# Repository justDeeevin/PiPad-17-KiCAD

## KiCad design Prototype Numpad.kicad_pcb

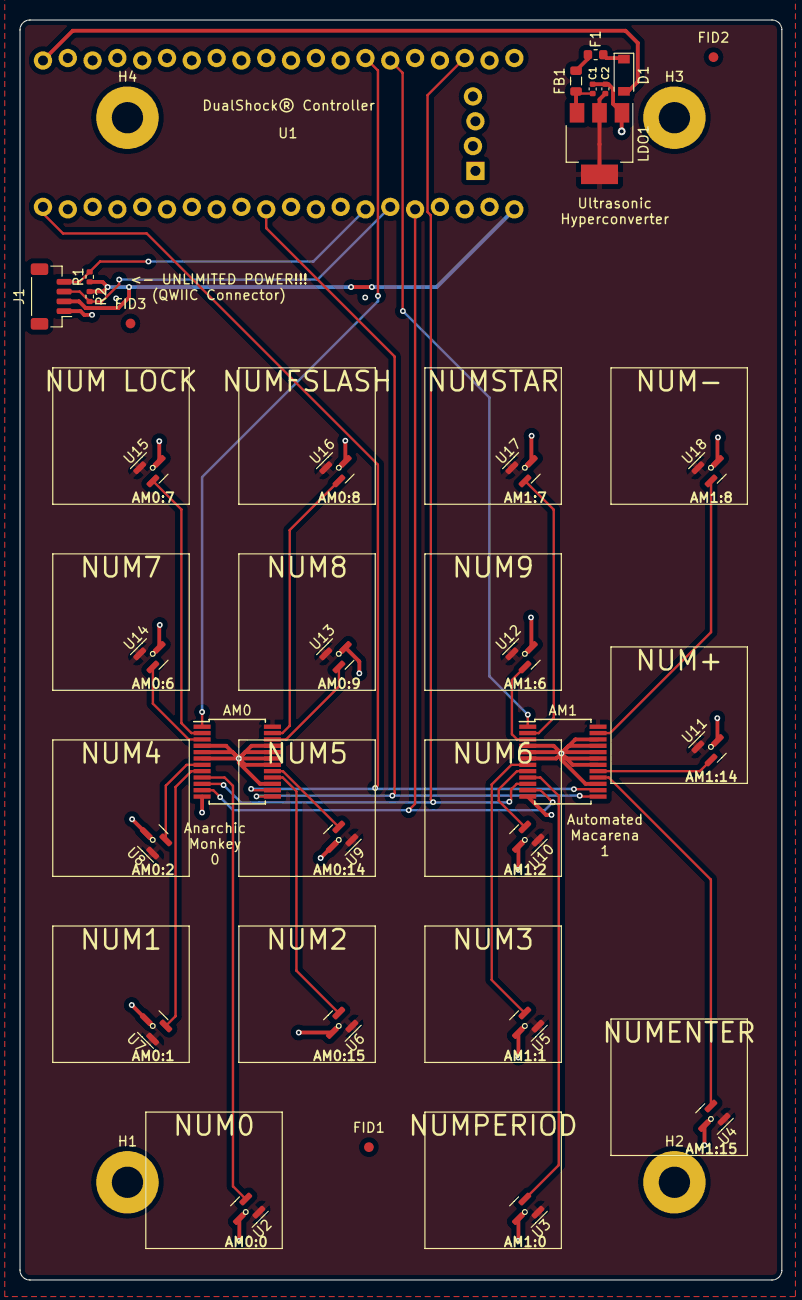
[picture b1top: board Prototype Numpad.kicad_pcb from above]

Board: 2 copper layers, 78.0 x 129.0 mm, 54 parts (1 on the bottom side), 32 nets.

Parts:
AM0, AM1: CD74HC4067SM; SSOP-24_5.3x8.2mm_P0.65mm
AM0:0: NUM0; VoidSwitch_2u_SMD
AM0:1: NUM1; VoidSwitch_1u_SMD
AM0:2: NUM4; VoidSwitch_1u_SMD
AM0:6: NUM7; VoidSwitch_1u_SMD
AM0:7: NUM LOCK; VoidSwitch_1u_SMD
AM0:8: NUMFSLASH; VoidSwitch_1u_SMD
AM0:9: NUM8; VoidSwitch_1u_SMD
AM0:14: NUM5; VoidSwitch_1u_SMD
AM0:15: NUM2; VoidSwitch_1u_SMD
AM1:0: NUMPERIOD; VoidSwitch_1u_SMD
AM1:1: NUM3; VoidSwitch_1u_SMD
AM1:2: NUM6; VoidSwitch_1u_SMD
AM1:6: NUM9; VoidSwitch_1u_SMD
AM1:7: NUMSTAR; VoidSwitch_1u_SMD
AM1:8: NUM-; VoidSwitch_1u_SMD
AM1:14: NUM+; VoidSwitch_2uv_SMD
AM1:15: NUMENTER; VoidSwitch_2uv_SMD
C1, C2: 10u; C_0402_1005Metric
D1: B5819W; D_SOD-123
F1: 500mA; Fuse_0603_1608Metric
FB1: 100 @ 100 MHz; L_0805_2012Metric
FID1, FID2, FID3: Fiducial; Fiducial_1mm_Mask2mm
H1, H2, H3, H4: MountingHole; MountingHole_3.2mm_M3_Pad
J1: QWIIC; JST_SH_BM04B-SRSS-TB_1x04-1MP_P1.00mm_Vertical
LDO1: AMS1117-3.3; SOT-223-3_TabPin2
QR*****: https://github.com/riskable/void_switch; VoidSwitch_Repo_QR_0.5mm
R1, R2: 2k2; R_0402_1005Metric
U1: BlackPill_STLINK
U2, U3, U4, U5, U6, U7, U8, U9, U10, U11, U12, U13, U14, U15, U16, U17, U18: GH39FKSW; SOT-23

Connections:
+3.3V_QWIIC: J1.2, R1.1, R2.1, U1.20 (3V3)
+3V3: AM0.24 (VCC), AM1.24 (VCC), C2.1, LDO1.2 (VO), U2.1 (VDD), U3.1 (VDD), U4.1 (VDD), U5.1 (VDD), U6.1 (VDD), U7.1 (VDD), U8.1 (VDD), U9.1 (VDD), U10.1 (VDD), U11.1 (VDD), U12.1 (VDD), U13.1 (VDD), U14.1 (VDD), U15.1 (VDD), U16.1 (VDD), U17.1 (VDD), U18.1 (VDD)
+5V: D1.2 (A), U1.40 (5V)
AM0: AM1.1 (COM), U1.26 (PA0)
AM0:0: AM0.9 (I0), U2.2 (OUT)
AM0:1: AM0.8 (I1), U7.2 (OUT)
AM0:2: AM0.7 (I2), U8.2 (OUT)
AM0:6: AM0.3 (I6), U14.2 (OUT)
AM0:7: AM0.2 (I7), U15.2 (OUT)
AM0:8: AM0.23 (I8), U16.2 (OUT)
AM0:9: AM0.22 (I9), U13.2 (OUT)
AM0:14: AM0.17 (I14), U9.2 (OUT)
AM0:15: AM0.16 (I15), U6.2 (OUT)
AM1: AM0.1 (COM), U1.27 (PA1)
AM1:0: AM1.9 (I0), U3.2 (OUT)
AM1:1: AM1.8 (I1), U10.2 (OUT)
AM1:2: AM1.7 (I2), U5.2 (OUT)
AM1:6: AM1.3 (I6), U12.2 (OUT)
AM1:7: AM1.2 (I7), U17.2 (OUT)
AM1:8: AM1.23 (I8), U18.2 (OUT)
AM1:14: AM1.17 (I14), U11.2 (OUT)
AM1:15: AM1.16 (I15), U4.2 (OUT)
GND: AM0.4 (I5), AM0.5 (I4), AM0.6 (I3), AM0.12 (GND), AM0.15 (~E), AM0.18 (I13), AM0.19 (I12), AM0.20 (I11), AM0.21 (I10), AM1.4 (I5), AM1.5 (I4), AM1.6 (I3), AM1.12 (GND), AM1.15 (~E), AM1.18 (I13), AM1.19 (I12), AM1.20 (I11), AM1.21 (I10), AM1.22 (I9), C1.2, C2.2, J1.1, LDO1.1 (GND), U1.19 (GND), U1.39 (GND), U1.44 (GND), U2.3 (GND), U3.3 (GND), U4.3 (GND), U5.3 (GND), U6.3 (GND), U7.3 (GND), U8.3 (GND), U9.3 (GND), U10.3 (GND), U11.3 (GND), U12.3 (GND), U13.3 (GND), U14.3 (GND), U15.3 (GND), U16.3 (GND), U17.3 (GND), U18.3 (GND)
unnamed: C1.1, FB1.1, LDO1.3 (VI)
unnamed: D1.1 (K), F1.1
unnamed: F1.2, FB1.2
PB6_SCL1: J1.4, R1.2, U1.14 (PB6)
PB7_SDA1: J1.3, R2.2, U1.15 (PB7)
SELECT0: AM0.10 (S0), AM1.10 (S0), U1.23 (PC14)
SELECT1: AM0.11 (S1), AM1.11 (S1), U1.16 (PB8)
SELECT2: AM0.14 (S2), AM1.14 (S2), U1.1 (PB12)
SELECT3: AM0.13 (S3), AM1.13 (S3), U1.10 (PA15)

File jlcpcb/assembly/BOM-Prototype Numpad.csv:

Comment,Designator,Footprint,LCSC
100 @ 100 MHz,FB1,L_0805_2012Metric,C1015
10u,"C1,C2",C_0402_1005Metric,C15525
QWIIC,J1,JST_SH_BM04B-SRSS-TB_1x04-1MP_P1.00mm_Vertical,C160404
2k2,"R1,R2",R_0402_1005Metric,C25879
500mA,F1,Fuse_0603_1608Metric,C261937
GH39FKSW,"U10,U11,U12,U13,U14,U15,U16,U17,U18,U2,U3,U4,U5,U6,U7,U8,U9",SOT-23,C266230
AMS1117-3.3,LDO1,SOT-223-3_TabPin2,C6186
B5819W,D1,D_SOD-123,C8598
CD74HC4067SM,AM0,SSOP-24_5.3x8.2mm_P0.65mm,
CD74HC4067SM,AM1,SSOP-24_5.3x8.2mm_P0.65mm,

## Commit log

2023-08-18 initialize repo on actual machine
